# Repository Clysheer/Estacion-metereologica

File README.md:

# Estacion-metereologica
La  Estación  Meteorológica  es  un  dispositivo  que  tiene  la  capacidad  de  medir  la temperatura  ambiente,  humedad  y  presión  atmosférica  del  lugar  específico  en  el  que  se encuentre  el  dispositivo  y  también  puede  visualizar  la  temperatura  de  una  zona geográfica  predeterminada  (ej:  Lomas  de  Zamora).  Todo  esto  utilizando  la  pantalla ST7789 de 240*240 pixeles que al ser oled mostrará al usuario los datos extraídos de manera fácil y sencilla. Todo esto utilizando como cerebro al microcontrolador ESP32que  utilizando  su  conexión  Wifi  logre  interactuar  con  la  utilización  de  una  API,  la  cual recibirá  los  datos  de  la  zona  geográfica  y  los  mostrará  por  la  pantalla,  y  además, utilizando  los  sensores  de  Presión  Atmosférica  BPM  180  y  el    DHT11  de  temperatura  y humedad  calcule  la  temperatura  del  ambiente  y  la  presión  atmosférica.
En  definitiva,  es  un  dispositivo  compuesto  por  un  microcontrolador  ESP32,  una  pantalla oled  y  unos  sensores  de  temperatura,  humedad  y  presión  atmosférica.
Al  tamaño  de  la  pantalla  ser  relativamente  pequeña,  los  datos  extraídos  del  sensor DHT11  y  de  la  API  se  irán  mostrando  por  la  pantalla  ST7789  en  manera  de  turnos, cada  15  segundo  pasará  de  mostrar  la  temperatura  ambiente  a  mostrar  la  meteorología de manera ciclica, así el usuario puede recibir ambas informaciones sin la necesidad de la utilizacion de un boton.
Todo esto será alimentado sin la utilización de baterías, si no que será alimentado mediante un cargador de 240v con una salida de 5v (cargador de celular) que ira conectado a la placa del dispositivo.
El  proyecto  está  planteado  como  un  proyecto  de  inicio,  el  costo  económico  no  es  muy alto  y  sirve  como  inicio  a  la  utilización  del  microcontrolador  ESP32  y  su  conectividad wifi.

*Diagrama  en  bloques:*

*Materiales :*

1-Pantalla DISPLAY TFT ST7789  240*240

2-ESP  WROOM  32  DEVKIT  V1

3-DHT11 Sensor Temperatura 

4-Placa  PCB  Simple  Faz  10x10

5-Sensor Presion Atmosferica Bmp180

*Diseño 3D :*

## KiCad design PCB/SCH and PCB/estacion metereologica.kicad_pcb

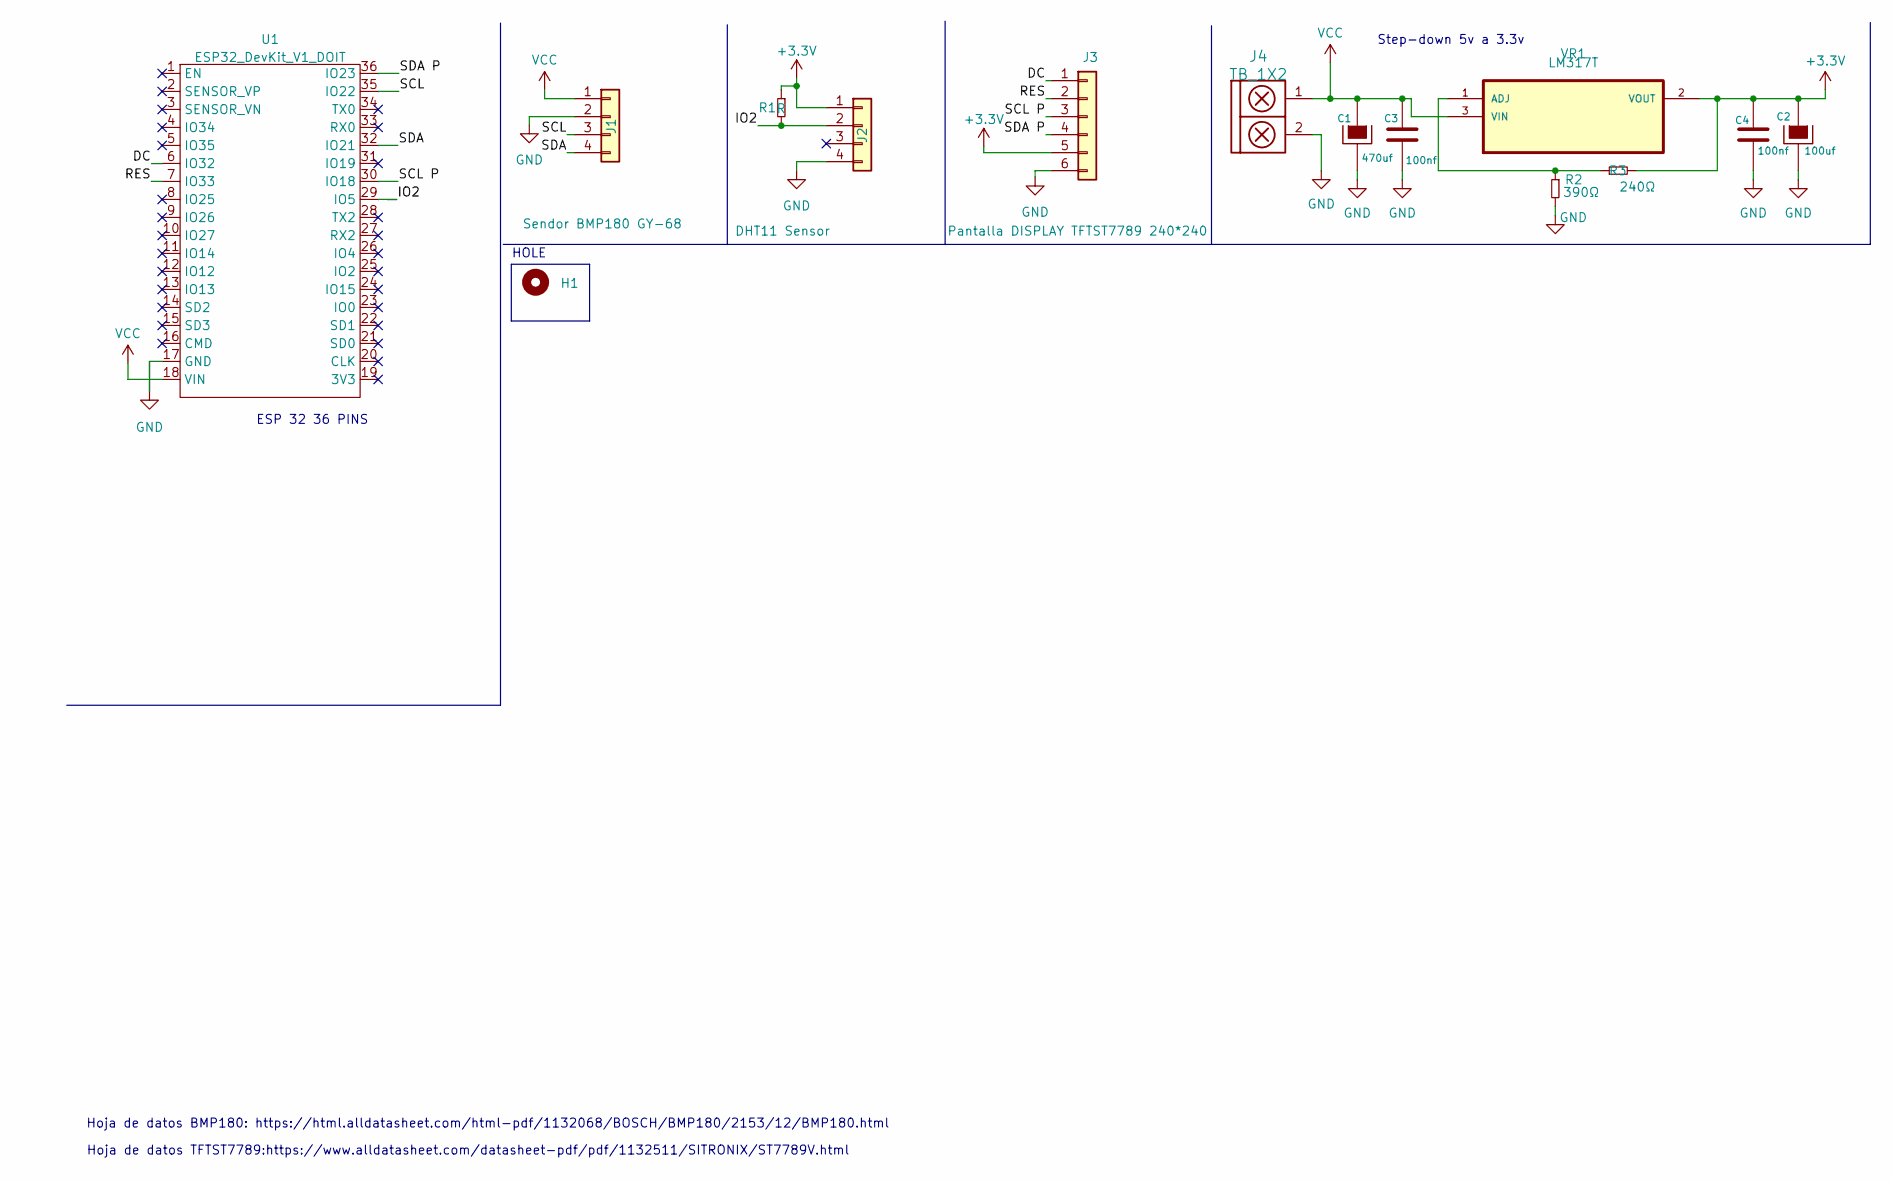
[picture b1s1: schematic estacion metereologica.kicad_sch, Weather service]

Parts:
C1: 470uf; CAP_ELEC_10X8mm
C2: 100uf; CAP_ELEC_5x11mm
C3, C4: 100nf; CP_Radial_Tantal_D4.5mm_P2.50mm
H1: Mounting_Hole; Tornillo_M3_8mm
J1: Sendor BMP180 GY-68; FanPinHeader_1x04_P2.54mm_Vertical
J2: DHT11 Sensor; FanPinHeader_1x04_P2.54mm_Vertical
J3: Pantalla DISPLAY TFTST7789 240*240; FanPinHeads_1x6_P2.54mm_Vertical
J4: TB_1X2; BORNERA2_AZUL
R1: R; RES0.3
R2: 390Ω; RES0.3
R3: 240Ω; RES0.3
U1: ESP32_DevKit_V1_DOIT; ESP32_DEVKIT_V1_DOIT
VR1: LM317T; TO254P1054X470X1955-3

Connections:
+3.3V: C2.1, C4.1, J2.1, J3.5, R1.1, R3.2, VR1.2 (VOUT)
/DC: J3.1, U1.6 (IO32)
/IO2: J2.2, R1.2, U1.29 (IO5)
/RES: J3.2, U1.7 (IO33)
/SCL: J1.3, U1.35 (IO22)
/SCL P: J3.3, U1.30 (IO18)
/SDA: J1.4, U1.32 (IO21)
/SDA P: J3.4, U1.36 (IO23)
GND: C1.2, C2.2, C3.2, C4.2, J1.2, J2.4, J3.6, J4.2, R2.2, U1.17 (GND)
unnamed: R2.1, R3.1, VR1.1 (ADJ)
VCC: C1.1, C3.1, J1.1, J4.1, U1.18 (VIN), VR1.3 (VIN)

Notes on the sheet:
Hoja de datos TFTST7789:https://www.alldatasheet.com/datasheet-pdf/pdf/1132511/SITRONIX/ST7789V.html
Step-down 5v a 3.3v
HOLE
Hoja de datos BMP180: https://html.alldatasheet.com/html-pdf/1132068/BOSCH/BMP180/2153/12/BMP180.html
ESP 32 36 PINS

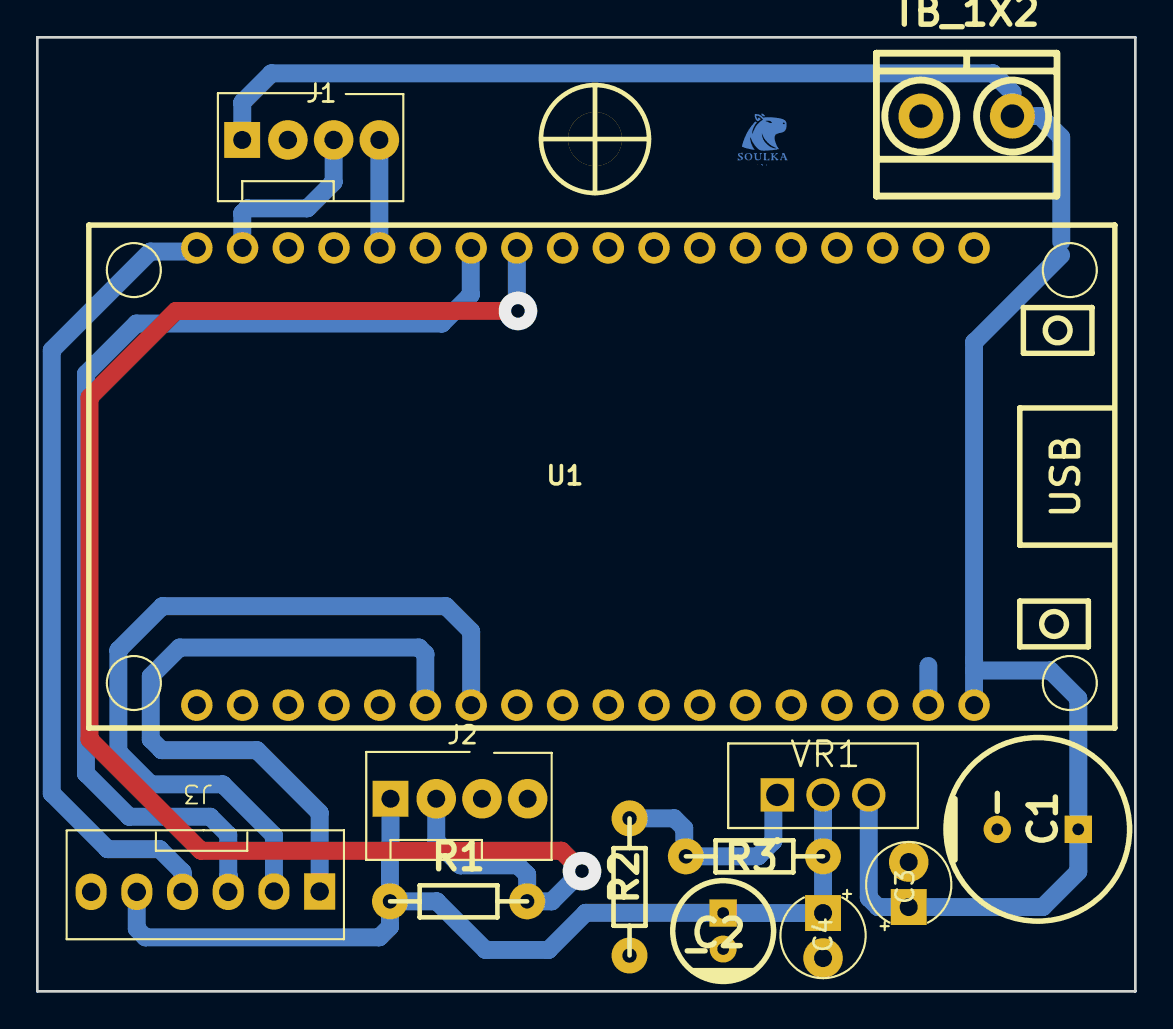
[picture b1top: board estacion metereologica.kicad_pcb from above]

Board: 2 copper layers, 61.0 x 53.0 mm, 14 parts (0 on the bottom side), 11 nets.

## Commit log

2024-04-29 Code Esp32 + API
    In this code the ESP32 microcontroller is connected with an API. This API is the weather service, their website is https://openweathermap.org. In this API you can obtain climate data from the geograp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
2024-04-29 Rename estacionm-serialprint.ino to wheather sevice-serial-print.ino
2024-05-13 PCB
    En esta carpeta se encuentran el esquemático y PCB del proyecto, además de la documentación de cada elemento utilizado.
    In this folder you will find the schematic and PCB of the project, as well as the documentation for each element used.
2024-05-13 estacionV1
2024-05-13 estacionV1.0
2024-05-13 PCB
    En esta carpeta se encuentra el esquemático y PCB del proyecto,además de su documentación
2024-05-14 estacion-metereologica.md
2024-06-18 Create README:md
2024-07-01 add pcb
2024-07-01 Add Diseño 3D
2024-07-03 archivos sin carpeta de la libreria
2024-07-03 libreria st7789 .zip
2024-07-08 EstacionMeteorologica
2024-10-14 Create estacion-serial-actualizada
2024-12-02 Rename EstacionMeteorologicaV7.1 to EstacionMeteorologicaV7.01.ino
2024-12-02 Rename estacion-serial-actualizada to estacion-serial-actualizada.ino
2024-12-02 Rename EstacionMeteorologica_V7.10.ino to .EstacionMeteorologica_V7.10.ino
2024-12-02 Rename .EstacionMeteorologica_V7.10.ino to EstacionMeteorologica_V7.10.ino
